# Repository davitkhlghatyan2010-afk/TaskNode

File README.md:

# Custom 6-Key Macropad with Rotary Encoder & OLED Display

A compact, DIY custom macropad built around the **Seeed Studio XIAO RP2040** microcontroller and running the open-source **KMK Firmware** (CircuitPython). This pad features 6 mechanical keyswitches, a 7-pixel chained SK6812 MINI-E RGB strip, a volume rotary encoder, and a sleek 0.91" SSD1306 128x32 OLED display running custom frame animations.

## 🧠 Why I Made This Project
I designed and constructed this custom 6-key macropad to bridge my interests in physical hardware engineering and digital automation. As someone diving deep into programming and data management, I wanted a physical desktop hub that could trigger specialized macro blocks on-the-fly, optimizing my coding speed while simultaneously teaching me the fundamentals of schematic routing, 3D mechanical enclosure assembly, and firmware layout.

## 🚀 Features
* **Dynamic JSON Configuration:** Keybinds are completely modular and loaded on-the-fly from a local `commands.json` file without modifying the main firmware.
* **Volume Rotary Encoder:** Clockwise/counterclockwise scroll tracking mapped to system volume adjustments.
* **Custom OLED Animations:** Bypasses default KMK layer readouts to loop custom 1-bit `.pbm` flipbook animations built for the compact 128x32 screen format.
* **RGB Breathing Effect:** Smooth breathing lighting profile across a 7-pixel SK6812 MINI-E LED chain.

---

## 🎨 Hardware Design, Schematics & Enclosure

### 📐 Schematic Diagrams
The circuit schematic handles direct GPIO switch tracking to keep the design highly responsive and simple, utilizing internal pull-up resistors on the RP2040.

### ⚡ Printed Circuit Board (PCB) Layout
The 2D PCB layout artwork is optimized for the tight form factor of the Seeed Studio XIAO footprint. Tracks are routed cleanly with thick power lines to safely drive the addressable RGB rail.

### 📦 Enclosure & Case Assembly
The enclosure is a low-profile design featuring heatset inserts for durable fastening. 

| Top Case Housing | Bottom Case Plate |
| :---: | :---: |
|  |  |

* **Layer Height:** 0.2mm
* **Infill:** 15% - 20% Gyroid (provides a solid weight distribution)
* **Hardware Requirements:** Requires 6x M3 heatset inserts melted into the top case housing, secured using 6x M3x16mm screws from the base plate.

---

## 📋 Bill of Materials (BOM)

The following matrix details the exact hardware required for assembly vs. the total material inventory available. You can also download the complete [BOM.csv](./BOM.csv) dataset directly from this repository.

| Item | Required Qty | Inventory Qty | Component Description | Sourcing / Part Notes |
| :---: | :---: | :---: | :--- | :--- |
| 1 | 1 | 1 | **Seeed Studio XIAO RP2040** | Main Microcontroller Board (Unsoldered) |
| 2 | 1 | 1 | **0.91" SSD1306 OLED Display** | 128x32 Pixel Screen, I2C Interface (**Pin order: GND-VCC-SCL-SDA**) |
| 3 | 1 | 2 | **EC11 Rotary Encoder** | 20mm D-Shaft Encoder |
| 4 | 6 | 16 | **MX-Style Mechanical Switches** | Keyswitches of choice |
| 5 | 6 | 16 | **Blank DSA Keycaps** | White full keycap set pack |
| 6 | 7 | 20 | **SK6812 MINI-E RGB LEDs** | Reverse-mount addressable LEDs |
| 7 | 6 | 6 | **M3×16mm Screws** | Enclosure fasteners |
| 8 | 6 | 6 | **M3×5×4mm Heatset Inserts** | Brass threaded chassis inserts |
| 9 | 0 | 20 | **1N4148 Diodes** | Through-hole matrix diodes (Unused in direct pin layout) |
| 10 | 1 | 1 | **Soldering Iron Station** | Required for assembly (Target temperature: 320°C - 350°C) |
| 11 | 1 | 1 | **Rosin Core Solder Wire** | 60/40 or Lead-Free electrical solder for making connections |
---

## 🛠️ Hardware Pinout Layout

The firmware maps directly to the following physical tracks on the Seeed Studio XIAO RP2040:

| Component | Pin / Track Assignment | Function |
| :--- | :--- | :--- |
| **SW1 (pos_1)** | `D9` | Mechanical Switch 1 |
| **SW2 (pos_2)** | `D8` | Mechanical Switch 2 |
| **SW3 (pos_3)** | `D3` | Mechanical Switch 3 |
| **SW4 (pos_4)** | `D10` | Mechanical Switch 4 |
| **SW5 (pos_5)** | `D0` | Mechanical Switch 5 |
| **SW6 (pos_6)** | `D2` | Mechanical Switch 6 |
| **NeoPixel Strip**| `D1` | 7-Pixel LED Data Line |
| **OLED SCL** | `D5` | I2C Clock Line |
| **OLED SDA** | `D4` | I2C Data Line |
| **Encoder Pad A**| `D6` | Quadrature Signal A |
| **Encoder Pad B**| `D7` | Quadrature Signal B |
| **Encoder Pad C**| `GND` | Common Ground Connection |

---

## 🤖 AI Usage Declaration
This project was developed using a collaborative approach between human engineering and artificial intelligence.

Concept & Exploration: AI was utilized as a learning accelerator to research and explore unfamiliar concepts, including schematic routing techniques, CircuitPython structures, and efficient data management with JSON.

Collaboration over Automation: While AI assisted in breaking down complex technical documentation and troubleshooting hardware configurations, all physical assembly, custom CAD design choices, and structural testing were executed entirely by the author.

---

## 📂 File Structure Explained

Your `CIRCUITPY` drive root should look like this:

```text
├── kmk/                  # KMK Firmware Library Folder
├── boot.py               # Hardware/USB-level configuration script
├── main.py               # Main Python firmware script (The core brain)
├── commands.json         # Dynamic keymap configuration profile
└── animation.pbm         # 128x32 compiled monochrome flipbook image strip

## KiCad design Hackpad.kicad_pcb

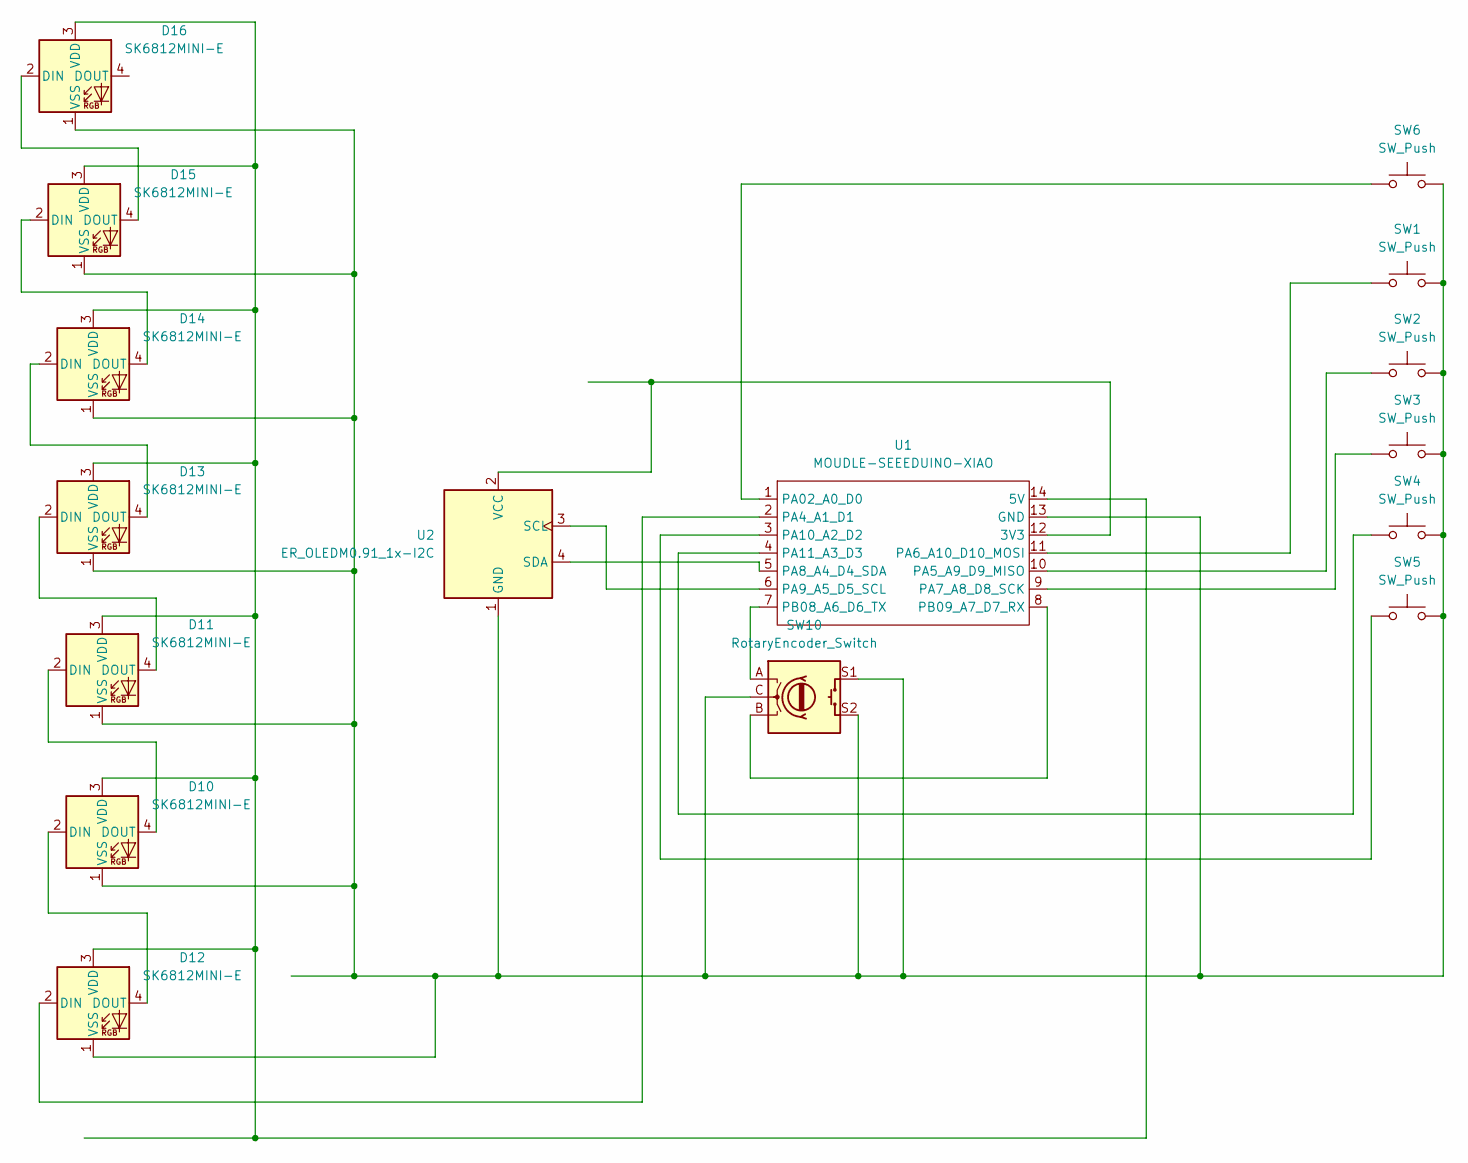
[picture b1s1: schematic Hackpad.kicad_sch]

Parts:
D10, D11, D12, D13, D14, D15, D16: SK6812MINI-E; LED_SK6812MINI-E_3.2x2.8mm_P1.5mm_ReverseMount
SW1, SW2, SW3, SW4, SW5, SW6: SW_Push; SW_Cherry_MX_1.00u_PCB
SW10: RotaryEncoder_Switch; RotaryEncoder_Alps_EC11E-Switch_Vertical_H20mm
U1: MOUDLE-SEEEDUINO-XIAO; XIAO-Generic-Hybrid-14P-2.54-21X17.8MM
U2: ER_OLEDM0.91_1x-I2C

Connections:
unnamed: D10.2 (DIN), D12.4 (DOUT)
unnamed: D10.4 (DOUT), D11.2 (DIN)
unnamed: D10.3 (VDD), D11.3 (VDD), D12.3 (VDD), D13.3 (VDD), D14.3 (VDD), D15.3 (VDD), D16.3 (VDD), U1.14 (5V)
unnamed: D10.1 (VSS), D11.1 (VSS), D12.1 (VSS), D13.1 (VSS), D14.1 (VSS), D15.1 (VSS), D16.1 (VSS), SW1.2, SW2.2, SW3.2, SW4.2, SW5.2, SW6.2, SW10.C, SW10.S1, SW10.S2, U1.13 (GND), U2.1 (GND)
unnamed: D11.4 (DOUT), D13.2 (DIN)
unnamed: D12.2 (DIN), U1.2 (PA4_A1_D1)
unnamed: D13.4 (DOUT), D14.2 (DIN)
unnamed: D14.4 (DOUT), D15.2 (DIN)
unnamed: D15.4 (DOUT), D16.2 (DIN)
unnamed: U1.12 (3V3), U2.2 (VCC)
unnamed: SW6.1, U1.1 (PA02_A0_D0)
unnamed: SW2.1, U1.10 (PA5_A9_D9_MISO)
unnamed: SW1.1, U1.11 (PA6_A10_D10_MOSI)
unnamed: SW3.1, U1.9 (PA7_A8_D8_SCK)
unnamed: U1.5 (PA8_A4_D4_SDA), U2.4 (SDA)
unnamed: U1.6 (PA9_A5_D5_SCL), U2.3 (SCL)
unnamed: SW5.1, U1.3 (PA10_A2_D2)
unnamed: SW4.1, U1.4 (PA11_A3_D3)
unnamed: SW10.A, U1.7 (PB08_A6_D6_TX)
unnamed: SW10.B, U1.8 (PB09_A7_D7_RX)

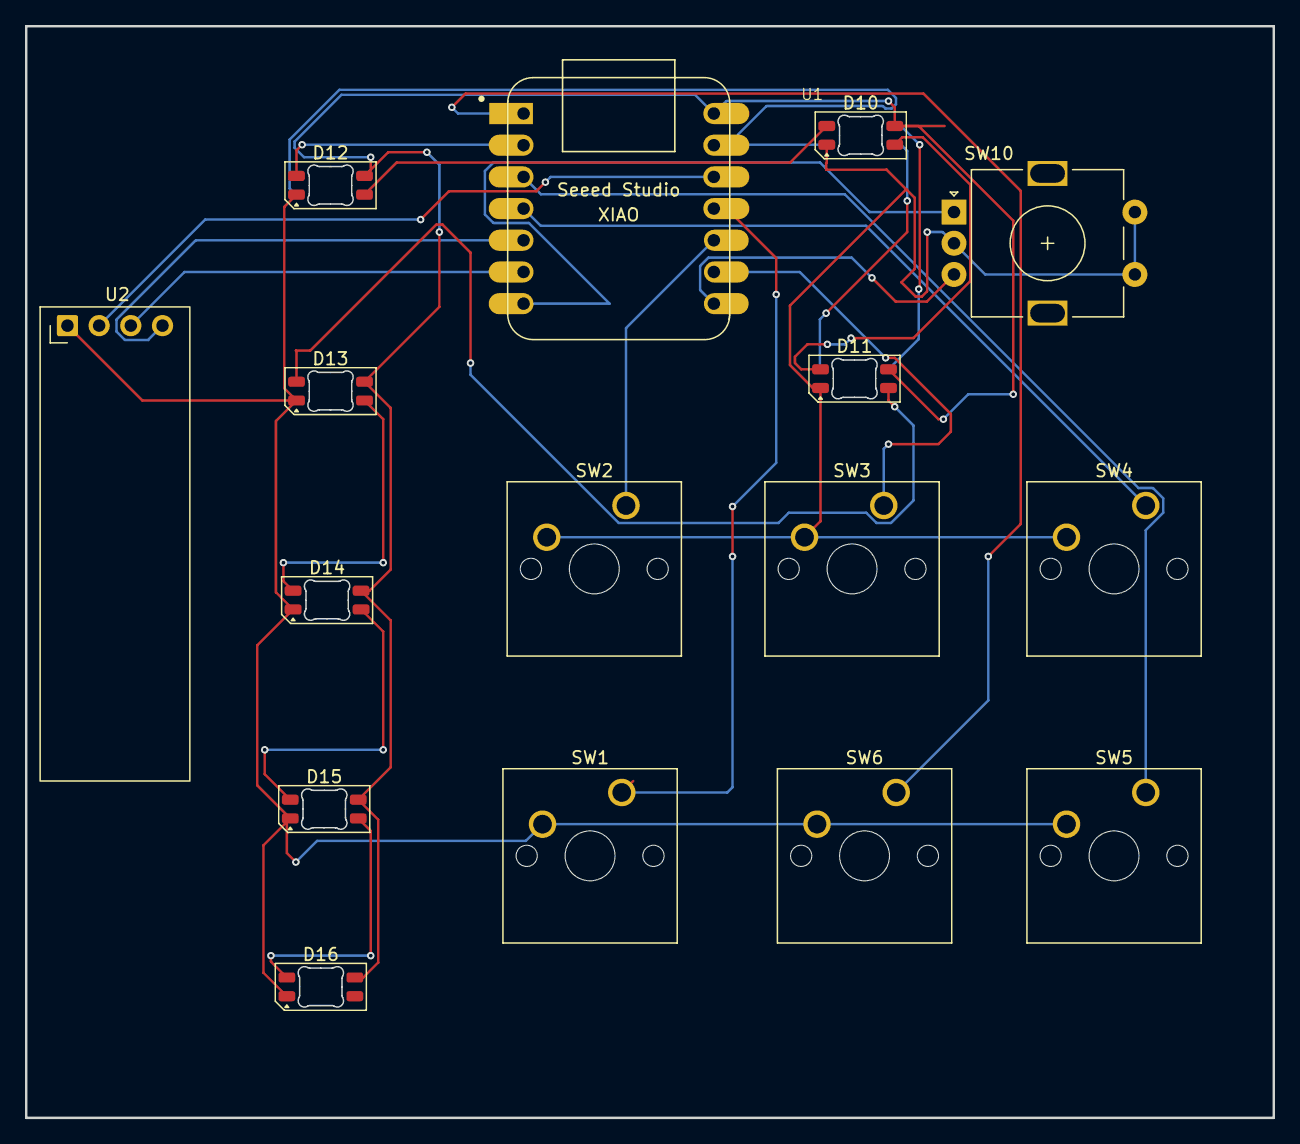
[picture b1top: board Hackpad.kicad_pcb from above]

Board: 2 copper layers, 100.0 x 87.5 mm, 16 parts (0 on the bottom side), 20 nets.

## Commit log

2026-06-18 Create smth
